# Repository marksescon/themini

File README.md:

# themini
Mini OD/Fuzz files

Disclaimer: Please double-check my work to ensure this circuit will work. I have built the pedal. It works. However, I cannot guarantee a fully functioning pedal and/or promise that the PCB is error-free. Proceed with caution. I am not responsible for any harm or injury that may arise from building this pedal. I have no association with the original builder/designer of the Mini. Product names are for comparison purposes only. For assistance troubleshooting, please refer to the multitude of online forums available like r/diypedals on Reddit.

Update - 07/172023

These are the files for fabricating a SSBS Mini clone through any services like JLCPCB or PCBWay.

General Documents:
- MINIPCB_BuildInstructions - build of materials, instructions for building including advice for a successful build
- SSBSMINISCHEMATIC.png - picture of the schematic

Files for any PCB design program like Eagle or KiCAD:
- SSBSMINI-THROUGHHOLE.brd - PCB for PCB CAD program
- SSBSMINI-THROUGHHOLE.sch - Schematic for PCB CAD program
- SSBSMini-PCBtraces.png - picture of the traces on the board

Alternatively, here is a link for an OshPark board: https://oshpark.com/shared_projects/tuJtiGCm.

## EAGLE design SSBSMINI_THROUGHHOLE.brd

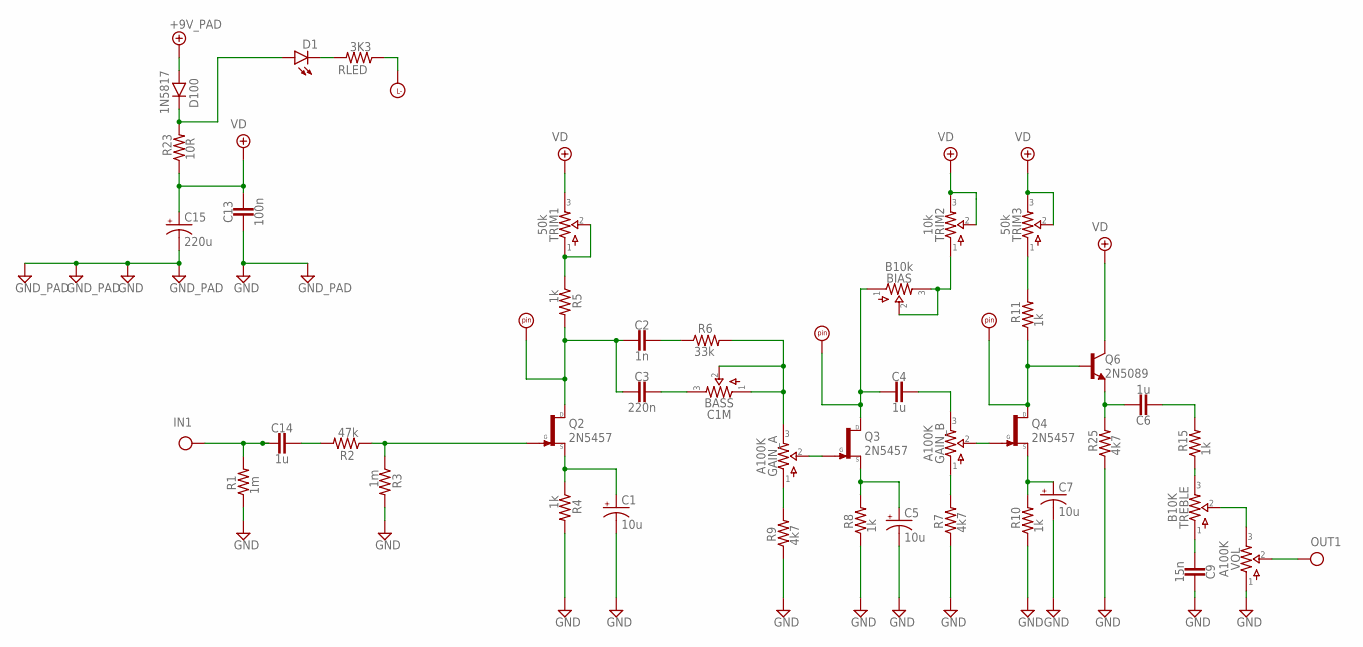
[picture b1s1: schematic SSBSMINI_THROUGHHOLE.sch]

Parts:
BASS: C1M; 16MM_B.MOUNT
BIAS: B10k; 16MM_B.MOUNT
C1, C5, C7: 10u; 050_020_1
C2: 1n; 0.2".SML
C3: 220n; 0.2".MED
C4, C6, C14: 1u; 0.2".MED
C9: 15n; 0.2".SML
C13: 100n; 0.2".SML
C15: 220u; 063_025_2
D1: LED3MM
D100: 1N5817; DO35-3
GAIN: A100K; 16MM_DUALGANG
GND1, GND17, GND18, GND19: GND_PAD; SQUARE
IN1: IN; SQUARE
LED: LED-; SQUARE
OUT1: OUT; SQUARE
Q2, Q3, Q4: 2N5457; TO92
Q6: 2N5089; TO92
R1, R3: 1m; R0204/2
R2: 47k; R0204/2
R4, R5, R8, R10, R11, R15: 1k; R0204/2
R6: 33k; R0204/2
R7, R9, R25: 4k7; R0204/2
R23: 10R; R0204/2
RLED: 3K3; R0204/2
TREBLE: B10K; 16MM_B.MOUNT
TRIM1, TRIM3: 50k; TRIM1
TRIM2: 10k; TRIM1
U$5, U$6, U$7: PADS.RND_NL; PAD2
V2: +9V_PAD; SQUARE
VOL: A100K; 16MM_B.MOUNT

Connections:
+9V: D100.A, V2.1
GND: C1.-, C5.-, C7.-, C9.1, C13.2, C15.-, GND1.1, GND17.1, GND18.1, GND19.1, R1.1, R3.2, R4.2, R7.1, R8.1, R9.1, R10.1, R25.1, VOL.1
IN: C14.2, IN1.1, R1.2
unnamed: R5.1, TRIM1.1, TRIM1.2
unnamed: C14.1, R2.2
unnamed: Q2.3 (G), R2.1, R3.1
unnamed: C1.+, Q2.2 (S), R4.1
unnamed: C2.2, C3.2, Q2.1 (D), R5.2, U$5.P$1
unnamed: C2.1, R6.1
unnamed: BASS.3, C3.1
unnamed: BASS.1, BASS.2, GAIN.3, R6.2
unnamed: GAIN.1, R9.2
unnamed: D1.A, D100.C, R23.2
unnamed: GAIN.2, Q3.3 (G)
unnamed: C5.+, Q3.2 (S), R8.2
unnamed: D1.K (C), RLED.2
unnamed: C4.1, GAIN.6 (3)
unnamed: GAIN.4 (1), R7.2
unnamed: C7.+, Q4.2 (S), R10.2
unnamed: Q4.1 (D), Q6.2 (B), R11.1, U$7.P$1
unnamed: GAIN.5 (2), Q4.3 (G)
unnamed: C6.1, Q6.3 (E), R25.2
unnamed: C6.2, R15.2
unnamed: R15.1, TREBLE.3
unnamed: C9.2, TREBLE.1
unnamed: TREBLE.2, VOL.3
unnamed: LED.1, RLED.1
unnamed: BIAS.2, BIAS.3, TRIM2.1
unnamed: BIAS.1, C4.2, Q3.1 (D), U$6.P$1
unnamed: R11.2, TRIM3.1
OUT: OUT1.1, VOL.2
VD: C13.1, C15.+, Q6.1 (C), R23.1, TRIM1.3, TRIM2.2, TRIM2.3, TRIM3.2, TRIM3.3

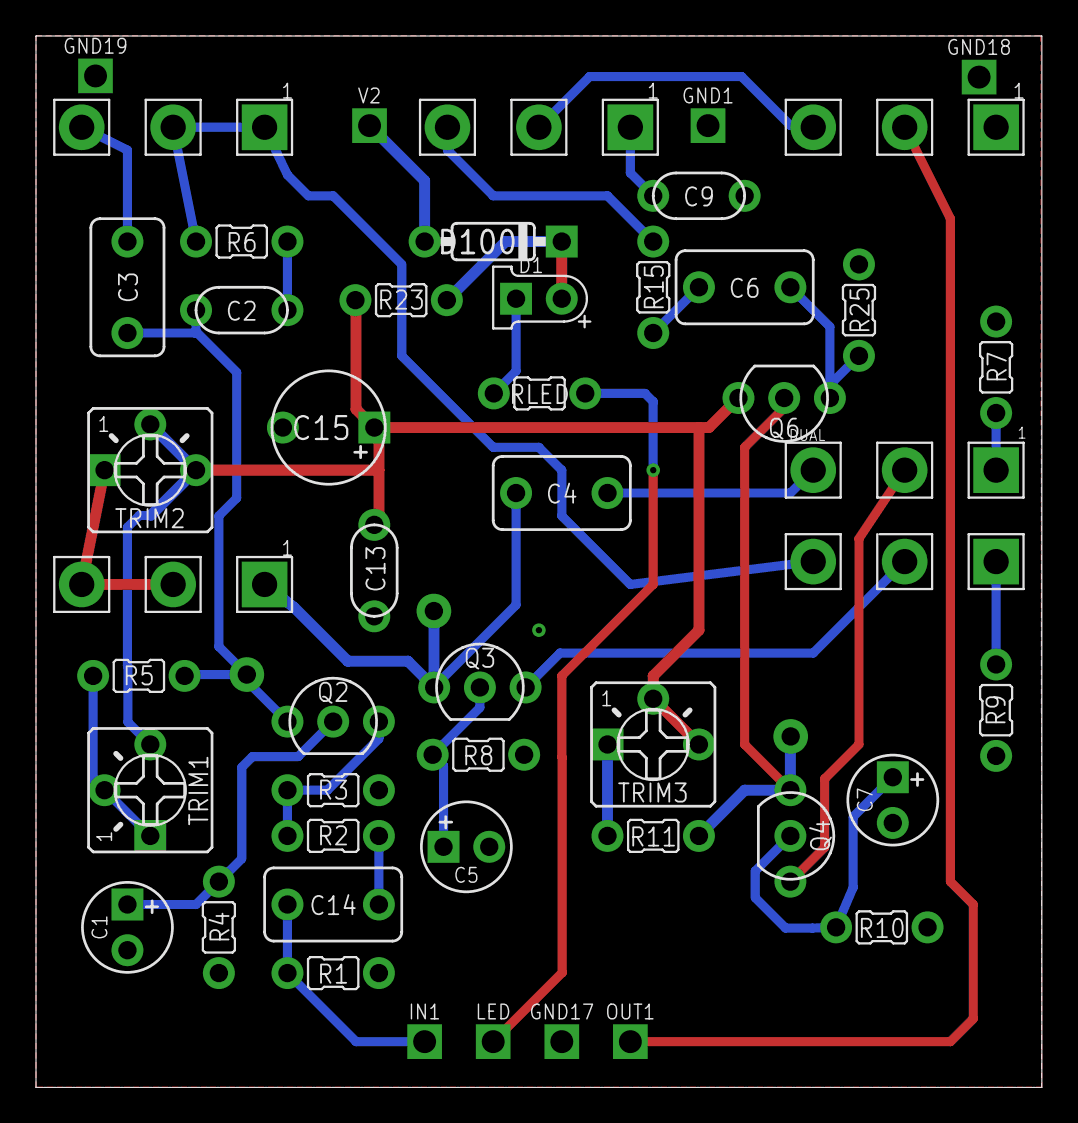
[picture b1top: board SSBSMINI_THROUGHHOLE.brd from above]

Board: 2 copper layers, 55.9 x 58.4 mm, 54 parts (1 on the bottom side), 32 nets.

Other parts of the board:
U$2: 3PDT
U$3, U$4: LUMBURG_TOP
